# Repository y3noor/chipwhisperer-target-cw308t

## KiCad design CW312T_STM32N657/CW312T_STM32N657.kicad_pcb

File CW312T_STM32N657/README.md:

# CW312T STM32N657, rev 01

This four-layer CW312 card uses the STM32N657X0H3Q in the 264-ball VFBGA. It has SWD, USART1, and a 512-Mbit external serial NOR flash. Open the KiCad 10 project to edit the schematic and PCB. The BOM and all 64 CW312 contacts are in `bom.csv` and `cw312-pinout.csv`.

**Fabrication hold.** Complete the electrical and layout checks below before release.

## Power

Use a sequenced bench supply at J1.

| Pin | Supply |
| --- | --- |
| 1 | Ground |
| 2 | 3.3 V for VDD, VBAT, and the debug voltage reference |
| 3 | 1.8 V for VDDA18AON, PDR_ON, and VDDA18PLL |
| 4 | 1.8 V input for the switched auxiliary rail |

The 3.3 V and 1.8 V main domains must meet AN5967 rev 6 section 3.5. Use the supply's tracking or trigger function and verify the ramps at TP7 and TP8. During power-up, the AON threshold crossing can follow the VDD threshold crossing by up to 250 µs. While either rail exceeds 0.6 V, keep AON within 50 mV above VDD. Apply the main group before the auxiliary group.

J5 pins 1–2 connect the MCU's PWR_ON to the auxiliary switch. PWR_ON goes high after the main group reaches its thresholds. U2 then provides the 1.8 V auxiliary rail for VDDSMPS, VDDA18PMU through FB1, VDDIO3, and the flash. The internal SMPS produces the core rail through L1. The SMPS uses local input capacitors, the output capacitor bank, and the R4/C5 snubber from the AN5967 topology. V08CAP has a dedicated capacitor. USB and ADC supplies and unused VDDIO2, VDDIO4, and VDDIO5 are tied to ground. CSI supplies are grounded and CSI signals are open.

For controlled shutdown, set J5 to OFF by removing the 1–2 shunt or installing it on 2–3. R2 holds the switch off with the shunt removed. U2 discharges the auxiliary rail through QOD. The AON-powered U4 sinks current through R9 to discharge the core rail. Keep the main rails within range until TP9 and TP10 are below 0.6 V. Then lower VDD and AON under tracking control as specified in AN5967 section 3.5.2. Verify the full sequence for controlled shutdown and loss of input before release.

CW313 passes Husky's 200 mA target supply to A5. ST's AN6000 tests the core converter with load steps to 700 mA. At 0.81 V, that step is 0.57 W. At 85% efficiency it would draw about 203 mA from 3.3 V before adding any I/O, memory, or startup load. This is a sizing case. Measure the actual current at startup and under load. The card leaves CW313 supply and shunt inputs open. A26 is the target's debug voltage reference. Use a probe with a voltage-sense input. Power down or disconnect external signal drivers before switching off the target. Set CW313 I/O to high impedance until the target rail is up.

R1 is the removable 0 Ω link in the 1.8 V auxiliary input. With power off, remove R1 and connect an ammeter between TP1 and TP2. This measures U2 input current, including the internal core converter, VDDIO3, and external flash. It excludes the 3.3 V and 1.8 V main rails. Monitor TP9 as you measure. The switch and meter both cause voltage drop.

## Bring-up

1. Keep all power off. Align the key with the CW313 slot. The MCU side faces the CW313 component side. Seat the card with the same orientation as the RP2350 reference.
2. Set J5 to OFF. Apply the main rails and confirm TP7, TP8, and PWR_ON at TP11. Set J5 to RUN with the 1–2 shunt. Check TP9 for the auxiliary rail and TP10 for the core rail. Check NRST at TP4. TP3 is ground.
3. For development boot, fit a shunt across J4 pins 3–4 to raise BOOT1 and leave pins 1–2 open. Reset the target. Connect ST-LINK with SWD. J2 pins 1 through 5 are VTREF, GND, SWDIO, SWCLK, and NRST. TP5 and TP6 expose SWDIO and SWCLK. The same debug signals are on CW313's Cortex connector. Use one probe.
4. For serial boot, remove the BOOT1 shunt. Fit a shunt across J4 pins 1–2 to raise BOOT0. Reset the target. Use the 3.3 V USART1 interface on J3. J3.1 is ground, J3.2 is target TX, and J3.3 is target RX. Keep the Husky TX output at high impedance if an external adapter drives RX. ST lists PE5 and PE6 as ROM USART1 pins. The device life cycle and OTP settings determine which ROM boot paths are available.
5. For flash boot, remove both J4 shunts. The resistors select BOOT0=0 and BOOT1=0. Use a first-stage bootloader with the STM32 header and a board-specific external loader for the MX25UM51245G. The ROM reads serial NOR on XSPI1 through XSPIM port 2. Use the default single-SPI protocol for first bring-up. Verify the XSPI loader and timing before enabling octal or double data rate modes.
6. The board has a 48 MHz HSE crystal. Use the internal clocks for initial SWD checks and verify the crystal starts before relying on it. C7 and C8 are initial load values from the Nucleo circuit. Adjust after measuring crystal loading and startup margin. R10 is a DNP link for a clock source at TP12. Remove Y1 if you fit R10 and configure HSE bypass. Use LSI when the firmware needs a low-speed clock.
7. Configure PG8 as an output for the trigger on CW312 B19. Set CW313 JP2 to GPIO4 and configure the capture-side pin as an input.

## Mechanical and layout checks

The 64 contact pads match the template and RP2350 pad dimensions and center offsets to 0.0001 mm resolution. The 1.00 mm pitch increases to 3.00 mm across the key. The tongue span is 34.30 mm. The contact lands are 0.70 × 4.20 mm. The A row is on the back and the B row is on the component side. The card is 1.60 mm thick for the CW313 Samtec -02 slot. The board outline and contact positions follow the CW312 template. The nearest fitted component is more than 4 mm from the end of a contact land. Confirm seating, insertion force, and probe access with a first article.

The BGA has a 14 × 14 mm body, a 0.80 mm grid, 0.40 mm lands, and 0.47 mm mask openings. The board uses four copper layers at 1.60 mm thickness. Layers 1 and 4 carry components, traces, and ground pours. Layer 2 carries the main ground pour and some traces. Layer 3 carries separate core and auxiliary supply pours and some traces. BGA escape uses plated through vias with a 0.20 mm minimum drill and a 0.125 mm minimum trace width. Check return paths around the traces and plane openings before fabrication.

KiCad 10.0.6 ERC and DRC report zero violations. DRC also reports zero unrouted pads and zero schematic parity issues.

The serial NOR has the same memory family and port assignment as the Nucleo design. This board uses the orderable SOIC-16W variant, with a 133 MHz part rating. The routed CLK, DQS, and IO0–IO7 copper lengths range from 6.10 to 25.25 mm, before via and package lengths. The Nucleo reference targets 1.27 mm matching for high-speed operation. The current routing requires length and return-path review before release. Confirm the PCB stackup and evaluate the flash timing at the intended clock rate with the selected assembly process. Review the core and auxiliary copper for IR drop at startup and full load. Verify the SMPS feedback route and snubber layout. Validate BGA solder mask and drill tolerances with the fabricator. No fabrication files are issued during the hold.

For the first article, verify the sequenced rise and discharge of all rails, HSE startup, SWD attachment, USART1 serial boot, flash identification and erase/write/read, flash boot, and current at idle and under load. Also verify the behavior when external signal cables are connected and the target powers down.

## References

- NewAE CW312 template rev 0, commit `40c337d2c8c15345bab03c9aa2072a23a36ccc3b`. The template license field says TBD. The CW312T_RP2350 rev 02 project is marked NDA. Contact and outline dimensions were measured and redrawn in KiCad.
- NewAE CW313 rev 02 schematic and PCB, commit `7b689277ca6852fccd195c29525a26640b6296d0`. The schematic title block states CC SA 3.0. [CW313 design files](https://github.com/newaetech/chipwhisperer-target-cw313/tree/7b689277ca6852fccd195c29525a26640b6296d0)
- Samtec PCIE-XXX-02-X-D-RA series drawing, sheets 1 and 2. [Connector drawing](https://suddendocs.samtec.com/prints/pcie-xxx-02-x-d-ra-mkt.pdf)
- ST MB1940-N657X0Q-C02, rev C-02. Sheets 3–5, 9, 12, and 14 cover I/O, power, flash, reset, and debug. The cover refers to ST's Open Platform License Agreement. The design uses reference circuit information and original KiCad artwork. [Nucleo schematic](https://www.st.com/resource/en/schematic_pack/mb1940-n657x0q-c02-schematic.pdf)
- ST DS14791 rev 11, plus the rev 2 package drawing and table 123 for the VFBGA264 land pattern. [STM32N657 datasheet](https://www.st.com/resource/en/datasheet/stm32n657x0.pdf)
- ST STM32 Open Pin Data, `mcu/STM32N657X0HxQ.xml`, commit `45c04599e2e0a788c5ed9b6218dc5a28a36041f7`. The symbol and footprint use the package's ball names and positions. See the included BSD 3-Clause license. [Pin data](https://github.com/STMicroelectronics/STM32_open_pin_data/blob/45c04599e2e0a788c5ed9b6218dc5a28a36041f7/mcu/STM32N657X0HxQ.xml)
- ST AN5967 rev 6, sections 3.4 through 3.6, for the power groups and timing. [Hardware development guide](https://www.st.com/resource/en/application_note/an5967-getting-started-with-hardware-development-for-stm32n6-mcus-stmicroelectronics.pdf)
- ST UM3234, serial NOR boot and USART1 pin assignment. [Boot ROM guide](https://www.st.com/resource/en/user_manual/um3234-how-to-proceed-with-boot-rom-on-stm32n6-mcus-stmicroelectronics.pdf)
- ST AN6000, core load transient specification. [Power supply guide](https://www.st.com/content/st_com/en/technical-documents/an6000-how-to-build-the-discrete-power-supply-for-stm32n6-mcus-stmicroelectronics.html)
- Macronix PM2183 rev 1.6, pin assignments, power, and ordering information. [Flash datasheet](https://www.macronix.com/Lists/Datasheet/Attachments/9241/MX25UM51245G%2C%201.8V%2C%20512Mb%2C%20v1.6.pdf)
- Texas Instruments SLVSD76C, TPS22918 load switch with QOD. [Load switch datasheet](https://www.ti.com/lit/ds/symlink/tps22918.pdf)

The ST-hosted PDF downloads for the Nucleo schematic and current datasheet, hardware guide, and boot ROM guide failed in this environment. Their contents were reviewed online. The local reference directory includes the available older ST revisions and the other downloaded reference PDFs.

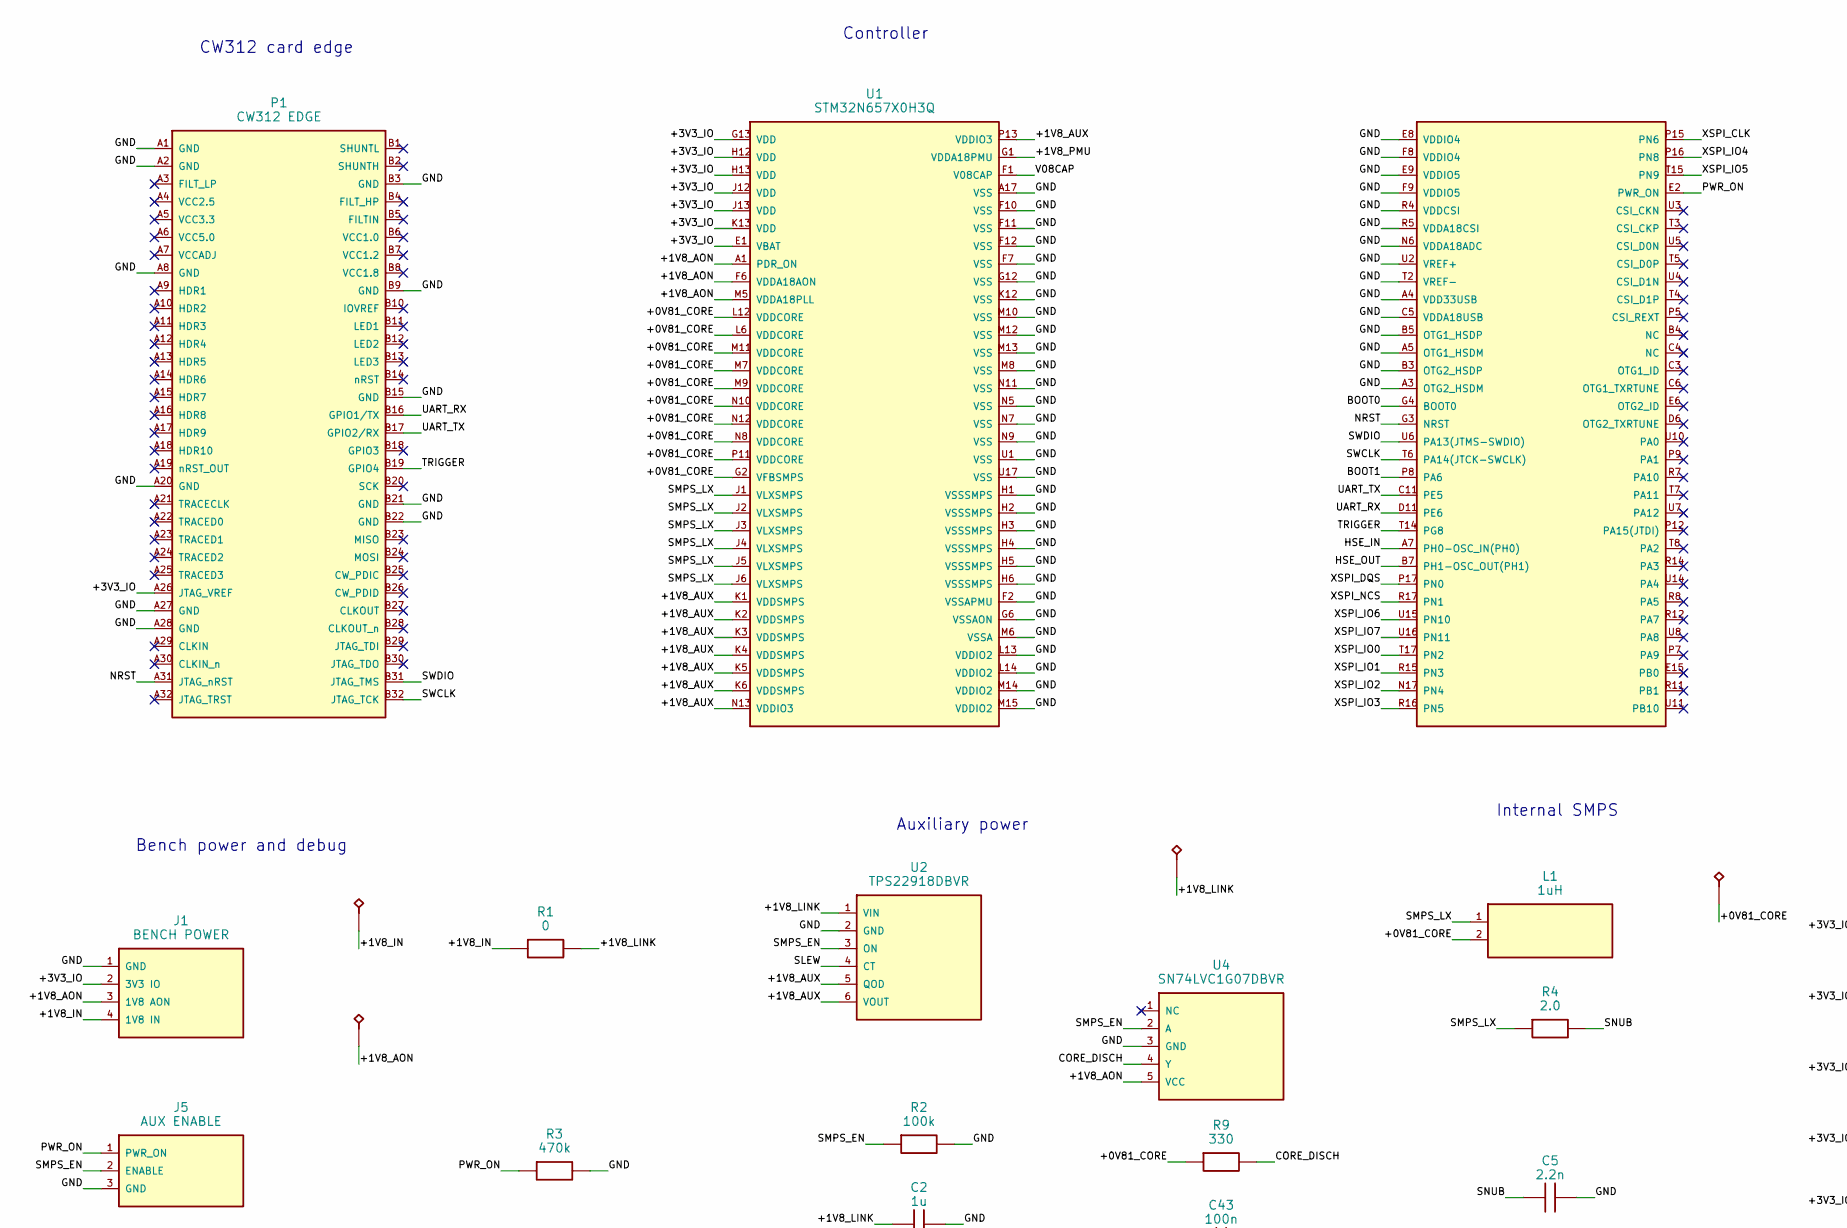
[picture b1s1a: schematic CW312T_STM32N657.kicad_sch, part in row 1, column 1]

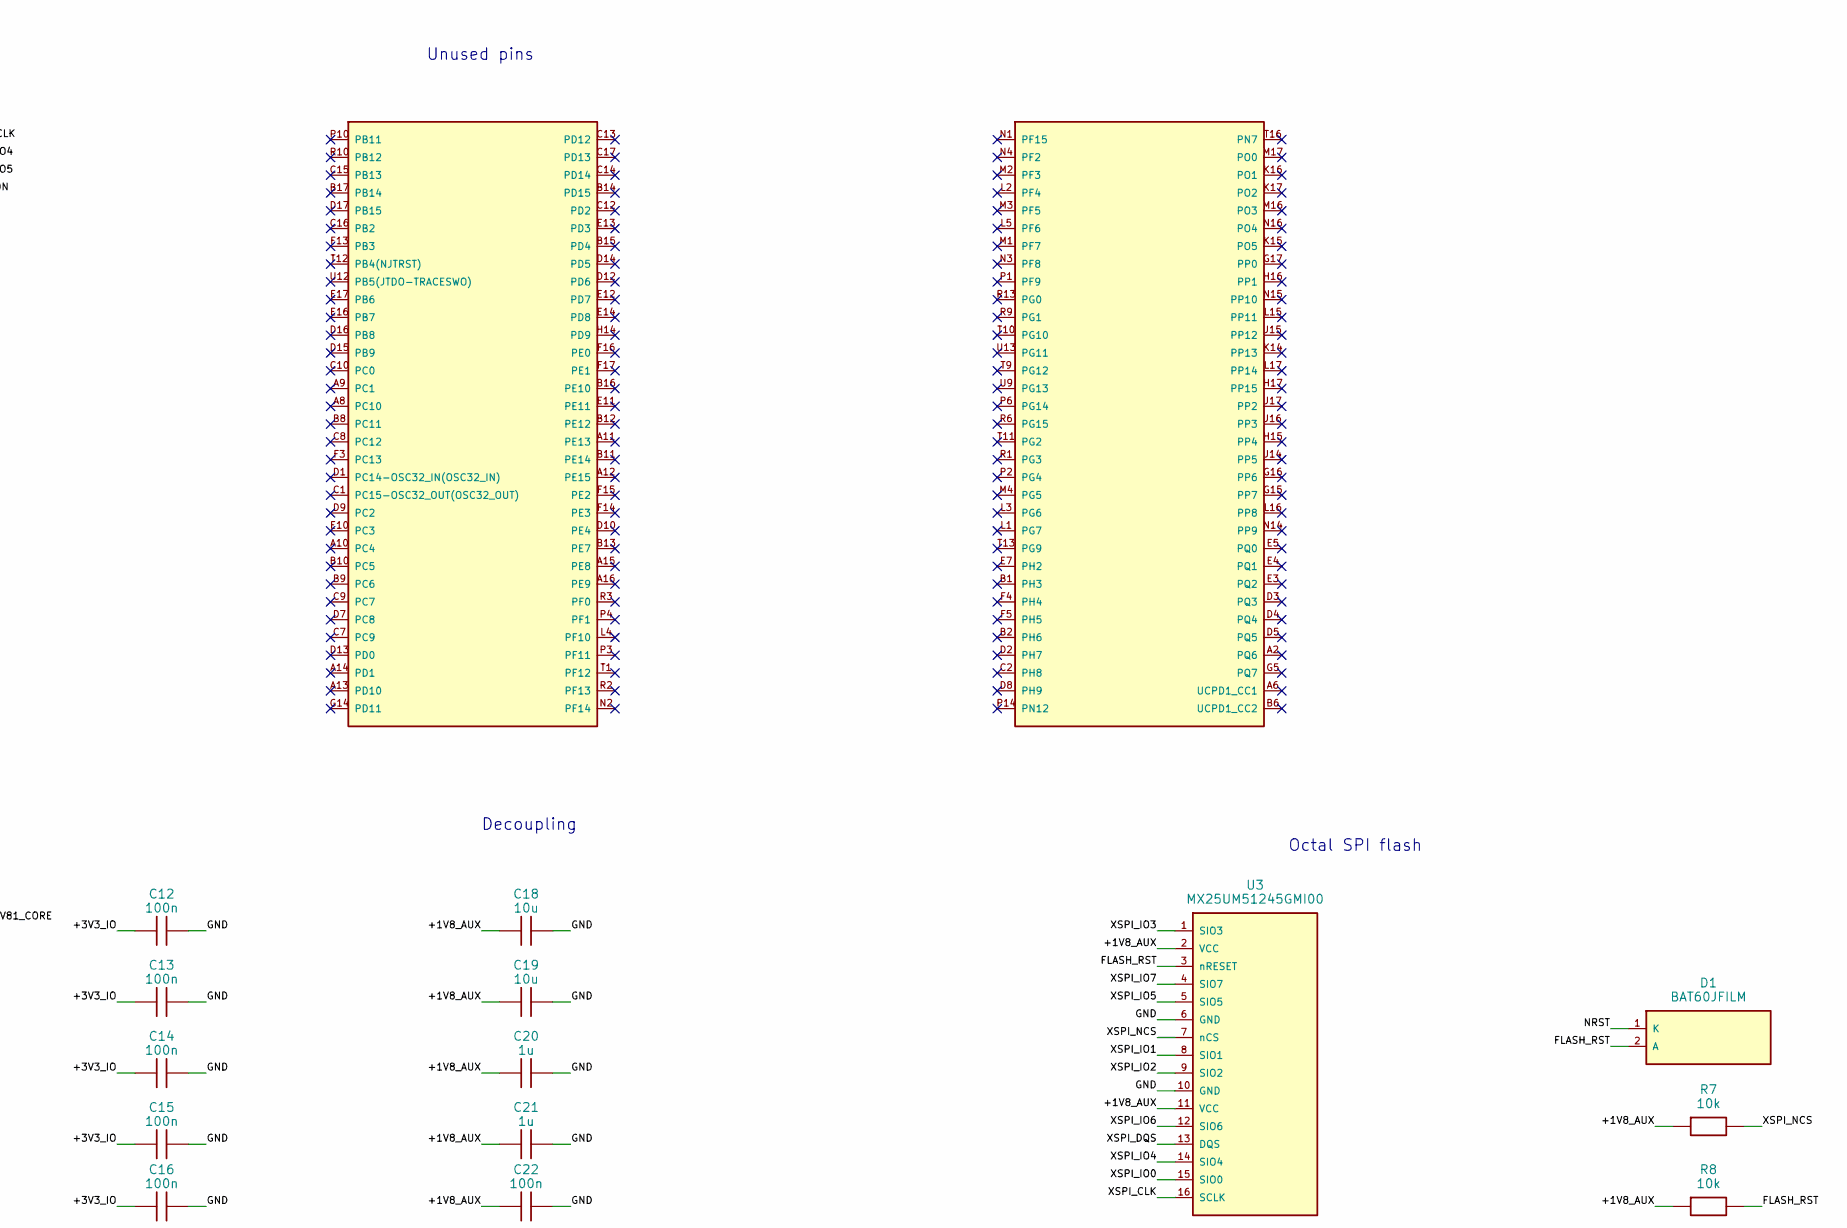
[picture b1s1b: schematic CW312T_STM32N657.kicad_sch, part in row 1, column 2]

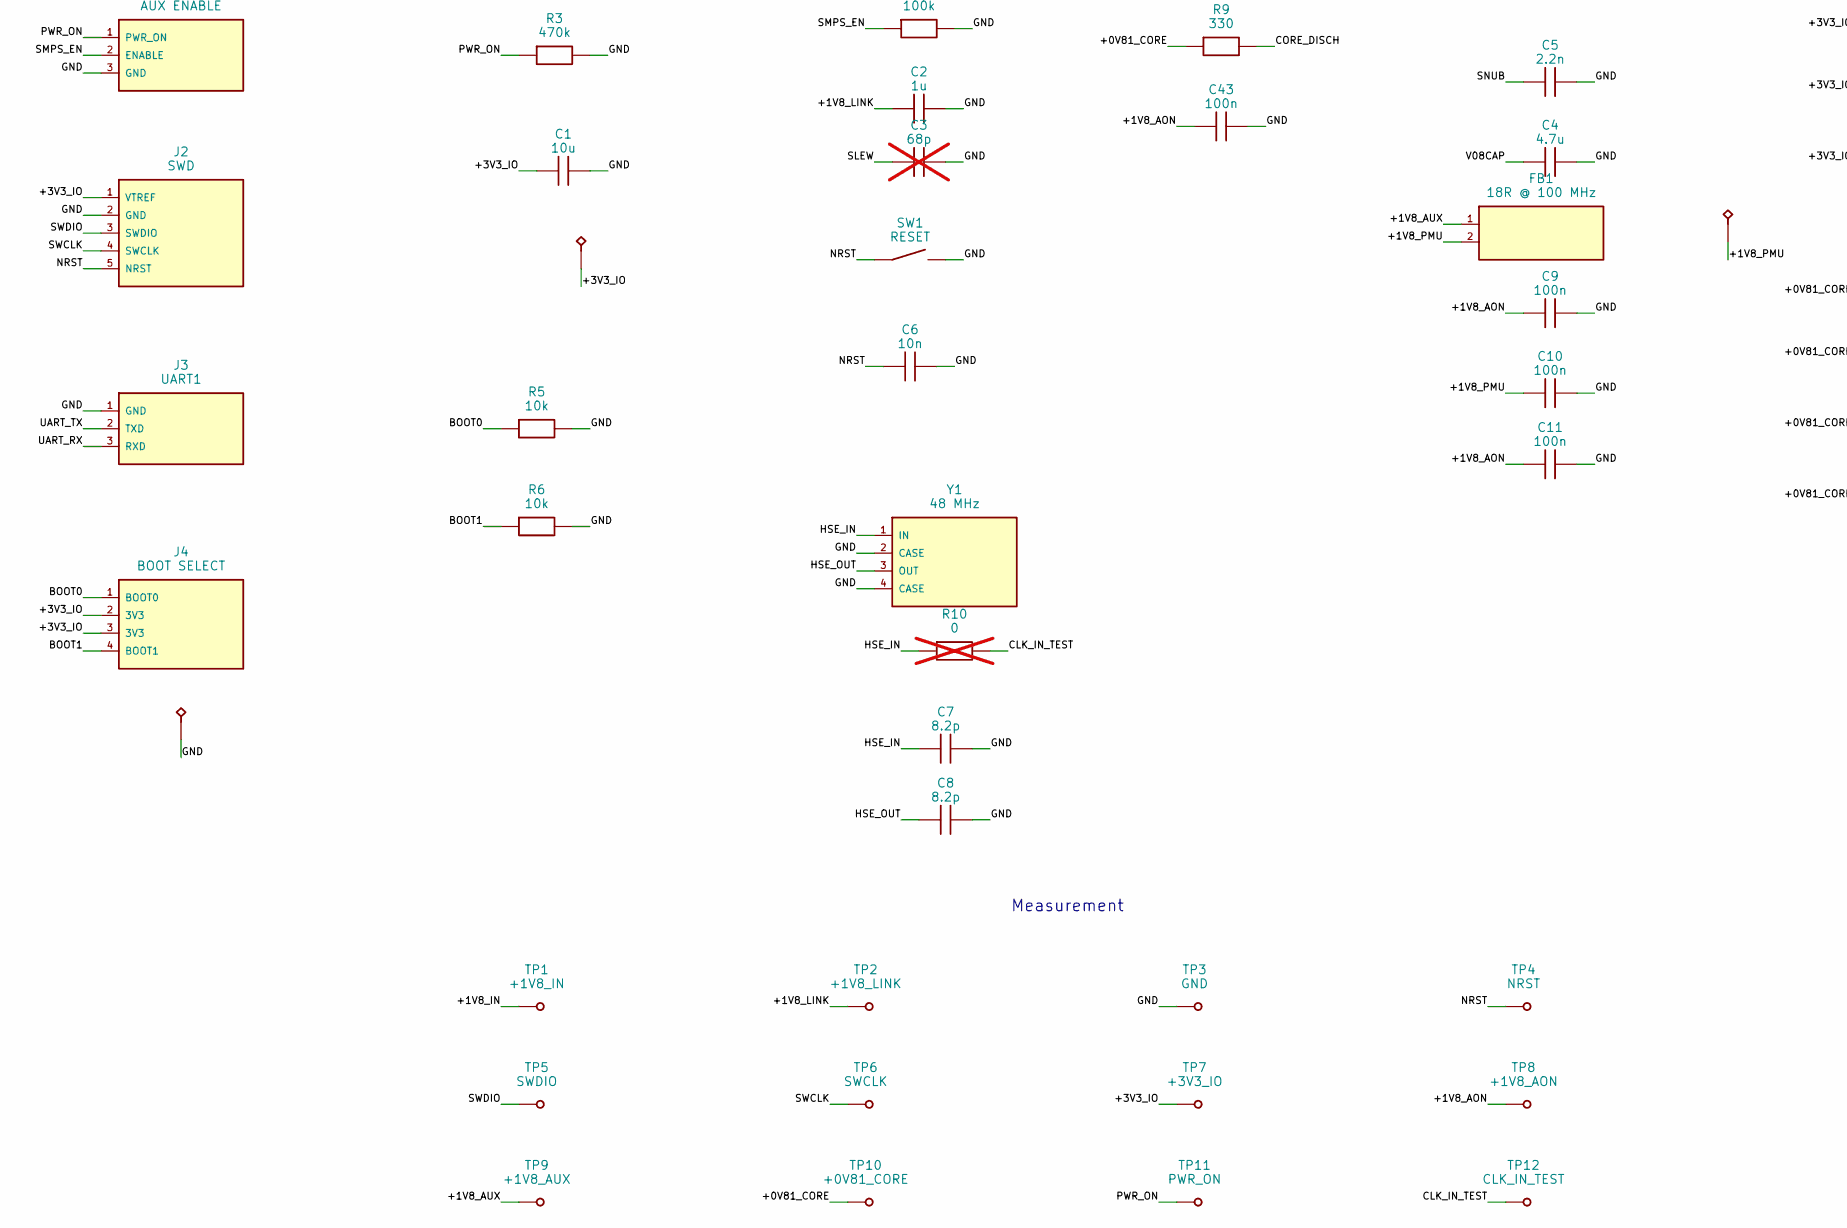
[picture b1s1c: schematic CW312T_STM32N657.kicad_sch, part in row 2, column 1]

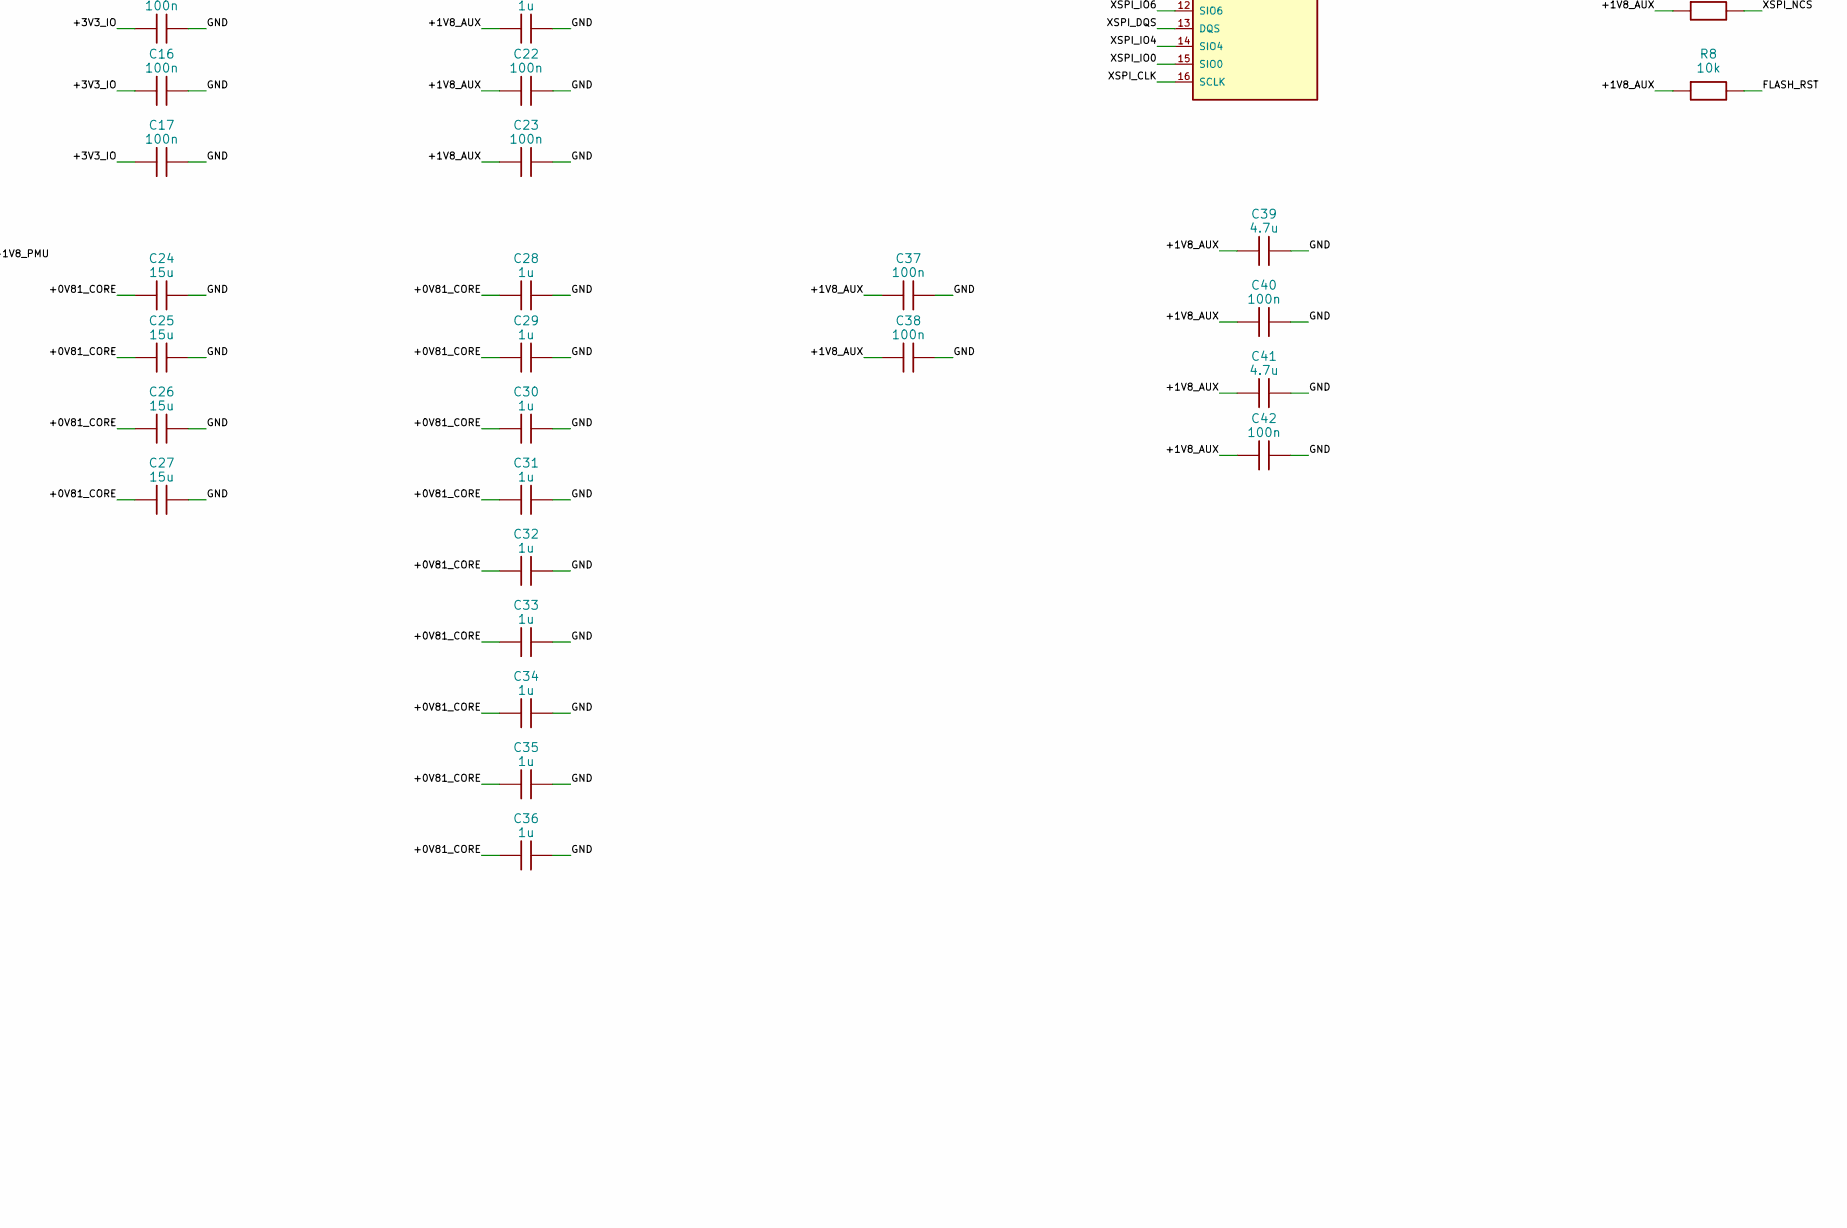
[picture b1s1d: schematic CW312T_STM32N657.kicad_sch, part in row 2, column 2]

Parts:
C1, C18, C19: 10u; C_0805_2012Metric
C2, C20, C21, C28, C29, C30, C31, C32, C33, C34, C35, C36: 1u; C_0402_1005Metric
C3: 68p; C_0402_1005Metric; not fitted
C4, C39, C41: 4.7u; C_0603_1608Metric
C5: 2.2n; C_0603_1608Metric
C6: 10n; C_0402_1005Metric
C7, C8: 8.2p; C_0402_1005Metric
C9, C10, C11, C12, C13, C14, C15, C16, C17, C22, C23, C37, C38, C40, C42, C43: 100n; C_0402_1005Metric
C24, C25, C26, C27: 15u; C_0805_2012Metric
D1: BAT60JFILM; D_SOD-323
FB1: 18R @ 100 MHz; L_0603_1608Metric
J1: BENCH POWER; PinHeader_1x04_P2.54mm_Vertical
J2: SWD; PinHeader_1x05_P2.54mm_Vertical
J3: UART1; PinHeader_1x03_P2.54mm_Vertical
J4: BOOT SELECT; PinHeader_1x04_P2.54mm_Vertical
J5: AUX ENABLE; PinHeader_1x03_P2.54mm_Vertical
L1: 1uH; L_1210_3225Metric
P1: CW312 EDGE; CW312
R1: 0; R_1206_3216Metric
R2: 100k; R_0603_1608Metric
R3: 470k; R_0603_1608Metric
R4: 2.0; R_0603_1608Metric
R5, R6, R7, R8: 10k; R_0603_1608Metric
R9: 330; R_0603_1608Metric
R10: 0; R_0603_1608Metric; not fitted
SW1: RESET; SW_Tactile_SPST_NO_Straight_CK_PTS636Sx25SMTRLFS
TP1: +1V8_IN; TestPoint_Pad_D1.5mm
TP2: +1V8_LINK; TestPoint_Pad_D1.5mm
TP3: GND; TestPoint_Pad_D1.5mm
TP4: NRST; TestPoint_Pad_D1.5mm
TP5: SWDIO; TestPoint_Pad_D1.5mm
TP6: SWCLK; TestPoint_Pad_D1.5mm
TP7: +3V3_IO; TestPoint_Pad_D1.5mm
TP8: +1V8_AON; TestPoint_Pad_D1.5mm
TP9: +1V8_AUX; TestPoint_Pad_D1.5mm
TP10: +0V81_CORE; TestPoint_Pad_D1.5mm
TP11: PWR_ON; TestPoint_Pad_D1.5mm
TP12: CLK_IN_TEST; TestPoint_Pad_D1.5mm
U1: STM32N657X0H3Q; ST_VFBGA-264_14x14mm_Layout17x17_P0.8mm
U2: TPS22918DBVR; SOT-23-6
U3: MX25UM51245GMI00; SOIC-16W_7.5x10.3mm_P1.27mm
U4: SN74LVC1G07DBVR; SOT-23-5
Y1: 48 MHz; Crystal_SMD_2016-4Pin_2.0x1.6mm

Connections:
/+0V81_CORE: C24.1, C25.1, C26.1, C27.1, C28.1, C29.1, C30.1, C31.1, C32.1, C33.1, C34.1, C35.1, C36.1, L1.2, R9.1, TP10.1, U1.G2 (VFBSMPS), U1.L6 (VDDCORE), U1.L12 (VDDCORE), U1.M7 (VDDCORE), U1.M9 (VDDCORE), U1.M11 (VDDCORE), U1.N8 (VDDCORE), U1.N10 (VDDCORE), U1.N12 (VDDCORE), U1.P11 (VDDCORE)
/+1V8_AON: C9.1, C11.1, C43.1, J1.3 (1V8_AON), TP8.1, U1.A1 (PDR_ON), U1.F6 (VDDA18AON), U1.M5 (VDDA18PLL), U4.5 (VCC)
/+1V8_AUX: C18.1, C19.1, C20.1, C21.1, C22.1, C23.1, C37.1, C38.1, C39.1, C40.1, C41.1, C42.1, FB1.1, R7.1, R8.1, TP9.1, U1.K1 (VDDSMPS), U1.K2 (VDDSMPS), U1.K3 (VDDSMPS), U1.K4 (VDDSMPS), U1.K5 (VDDSMPS), U1.K6 (VDDSMPS), U1.N13 (VDDIO3), U1.P13 (VDDIO3), U2.5 (QOD), U2.6 (VOUT), U3.2 (VCC), U3.11 (VCC)
/+1V8_IN: J1.4 (1V8_IN), R1.1, TP1.1
/+1V8_LINK: C2.1, R1.2, TP2.1, U2.1 (VIN)
/+1V8_PMU: C10.1, FB1.2, U1.G1 (VDDA18PMU)
/+3V3_IO: C1.1, C12.1, C13.1, C14.1, C15.1, C16.1, C17.1, J1.2 (3V3_IO), J2.1 (VTREF), J4.2 (3V3), J4.3 (3V3), P1.A26 (JTAG_VREF), TP7.1, U1.E1 (VBAT), U1.G13 (VDD), U1.H12 (VDD), U1.H13 (VDD), U1.J12 (VDD), U1.J13 (VDD), U1.K13 (VDD)
/BOOT0: J4.1 (BOOT0), R5.1, U1.G4 (BOOT0)
/BOOT1: J4.4 (BOOT1), R6.1, U1.P8 (PA6)
/CLK_IN_TEST: R10.2, TP12.1
/CORE_DISCH: R9.2, U4.4 (Y)
/FLASH_RST: D1.2 (A), R8.2, U3.3 (nRESET)
/GND: C1.2, C2.2, C3.2, C4.2, C5.2, C6.2, C7.2, C8.2, C9.2, C10.2, C11.2, C12.2, C13.2, C14.2, C15.2, C16.2, C17.2, C18.2, C19.2, C20.2, C21.2, C22.2, C23.2, C24.2, C25.2, C26.2, C27.2, C28.2, C29.2, C30.2, C31.2, C32.2, C33.2, C34.2, C35.2, C36.2, C37.2, C38.2, C39.2, C40.2, C41.2, C42.2, C43.2, J1.1 (GND), J2.2 (GND), J3.1 (GND), J5.3 (GND), P1.A1 (GND), P1.A2 (GND), P1.A8 (GND), P1.A20 (GND), P1.A27 (GND), P1.A28 (GND), P1.B3 (GND), P1.B9 (GND), P1.B15 (GND), P1.B21 (GND), P1.B22 (GND), R2.2, R3.2, R5.2, R6.2, SW1.2, TP3.1, U1.A3 (OTG2_HSDM), U1.A4 (VDD33USB), U1.A5 (OTG1_HSDM), U1.A17 (VSS), U1.B3 (OTG2_HSDP), U1.B5 (OTG1_HSDP), U1.C5 (VDDA18USB), U1.E8 (VDDIO4), U1.E9 (VDDIO5), U1.F2 (VSSAPMU), U1.F7 (VSS), U1.F8 (VDDIO4), U1.F9 (VDDIO5), U1.F10 (VSS), U1.F11 (VSS), U1.F12 (VSS), U1.G6 (VSSAON), U1.G12 (VSS), U1.H1 (VSSSMPS), U1.H2 (VSSSMPS), U1.H3 (VSSSMPS), U1.H4 (VSSSMPS), U1.H5 (VSSSMPS), U1.H6 (VSSSMPS), U1.K12 (VSS), U1.L13 (VDDIO2), U1.L14 (VDDIO2), U1.M6 (VSSA), U1.M8 (VSS), U1.M10 (VSS), U1.M12 (VSS), U1.M13 (VSS), U1.M14 (VDDIO2), U1.M15 (VDDIO2), U1.N5 (VSS), U1.N6 (VDDA18ADC), U1.N7 (VSS), U1.N9 (VSS), U1.N11 (VSS), U1.R4 (VDDCSI), U1.R5 (VDDA18CSI), U1.T2 (VREF-), U1.U1 (VSS), U1.U2 (VREF+), U1.U17 (VSS), U2.2 (GND), U3.6 (GND), U3.10 (GND), U4.3 (GND), Y1.2 (CASE), Y1.4 (CASE)
/HSE_IN: C7.1, R10.1, U1.A7 (PH0-OSC_IN(PH0)), Y1.1 (IN)
/HSE_OUT: C8.1, U1.B7 (PH1-OSC_OUT(PH1)), Y1.3 (OUT)
/NRST: C6.1, D1.1 (K), J2.5 (NRST), P1.A31 (JTAG_nRST), SW1.1, TP4.1, U1.G3 (NRST)
/PWR_ON: J5.1 (PWR_ON), R3.1, TP11.1, U1.E2 (PWR_ON)
/SLEW: C3.1, U2.4 (CT)
/SMPS_EN: J5.2 (ENABLE), R2.1, U2.3 (ON), U4.2 (A)
/SMPS_LX: L1.1, R4.1, U1.J1 (VLXSMPS), U1.J2 (VLXSMPS), U1.J3 (VLXSMPS), U1.J4 (VLXSMPS), U1.J5 (VLXSMPS), U1.J6 (VLXSMPS)
/SNUB: C5.1, R4.2
/SWCLK: J2.4 (SWCLK), P1.B32 (JTAG_TCK), TP6.1, U1.T6 (PA14(JTCK-SWCLK))
/SWDIO: J2.3 (SWDIO), P1.B31 (JTAG_TMS), TP5.1, U1.U6 (PA13(JTMS-SWDIO))
/TRIGGER: P1.B19 (GPIO4), U1.T14 (PG8)
/UART_RX: J3.3 (RXD), P1.B16 (GPIO1/TX), U1.D11 (PE6)
/UART_TX: J3.2 (TXD), P1.B17 (GPIO2/RX), U1.C11 (PE5)
/V08CAP: C4.1, U1.F1 (V08CAP)
/XSPI_CLK: U1.P15 (PN6), U3.16 (SCLK)
/XSPI_DQS: U1.P17 (PN0), U3.13 (DQS)
/XSPI_IO0: U1.T17 (PN2), U3.15 (SIO0)
/XSPI_IO1: U1.R15 (PN3), U3.8 (SIO1)
/XSPI_IO2: U1.N17 (PN4), U3.9 (SIO2)
/XSPI_IO3: U1.R16 (PN5), U3.1 (SIO3)
/XSPI_IO4: U1.P16 (PN8), U3.14 (SIO4)
/XSPI_IO5: U1.T15 (PN9), U3.5 (SIO5)
/XSPI_IO6: U1.U15 (PN10), U3.12 (SIO6)
/XSPI_IO7: U1.U16 (PN11), U3.4 (SIO7)
/XSPI_NCS: R7.2, U1.R17 (PN1), U3.7 (nCS)

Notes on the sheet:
CW312 card edge
Controller
Unused pins
Bench power and debug
Auxiliary power
Internal SMPS
Decoupling
Octal SPI flash
Measurement

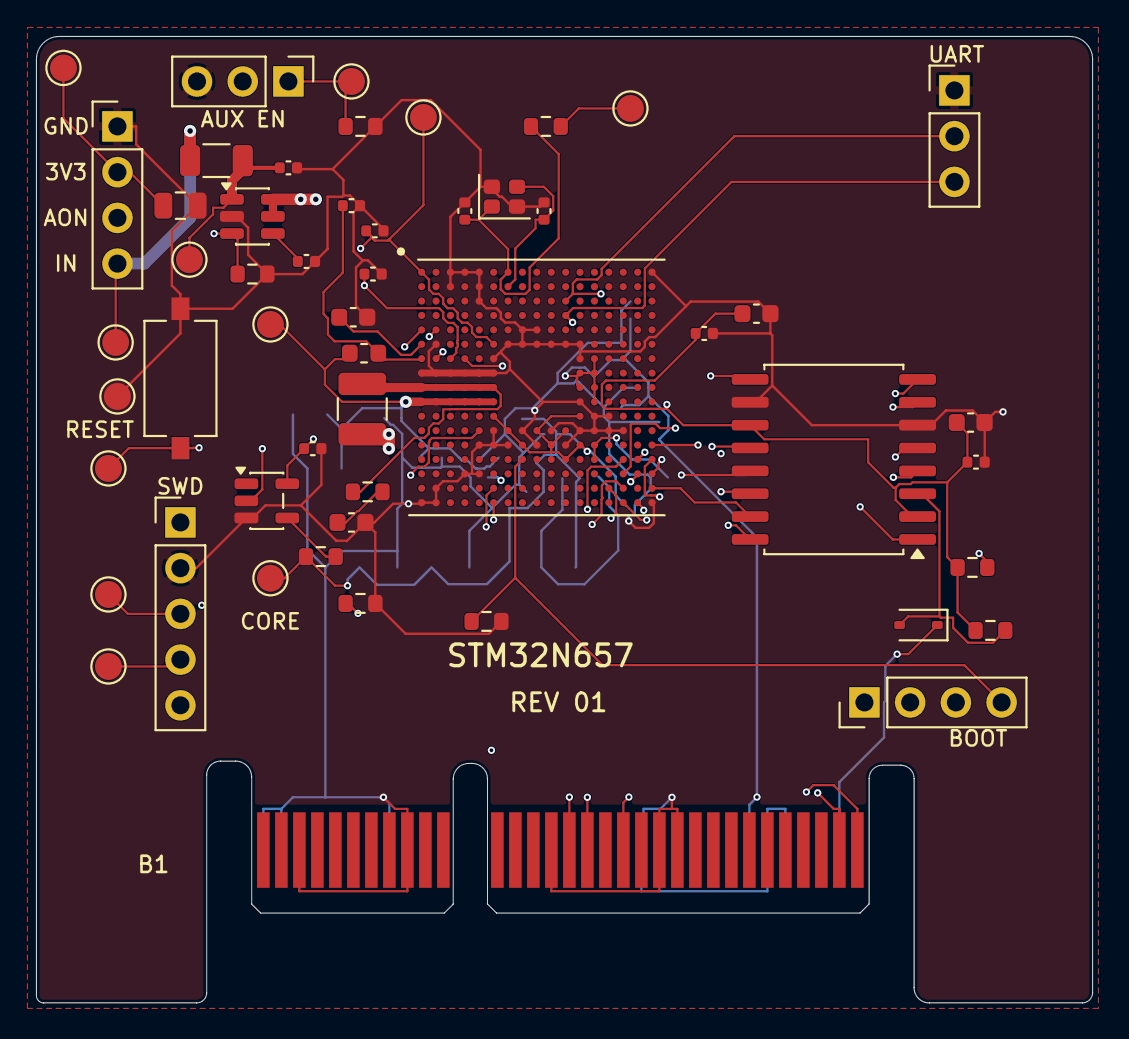
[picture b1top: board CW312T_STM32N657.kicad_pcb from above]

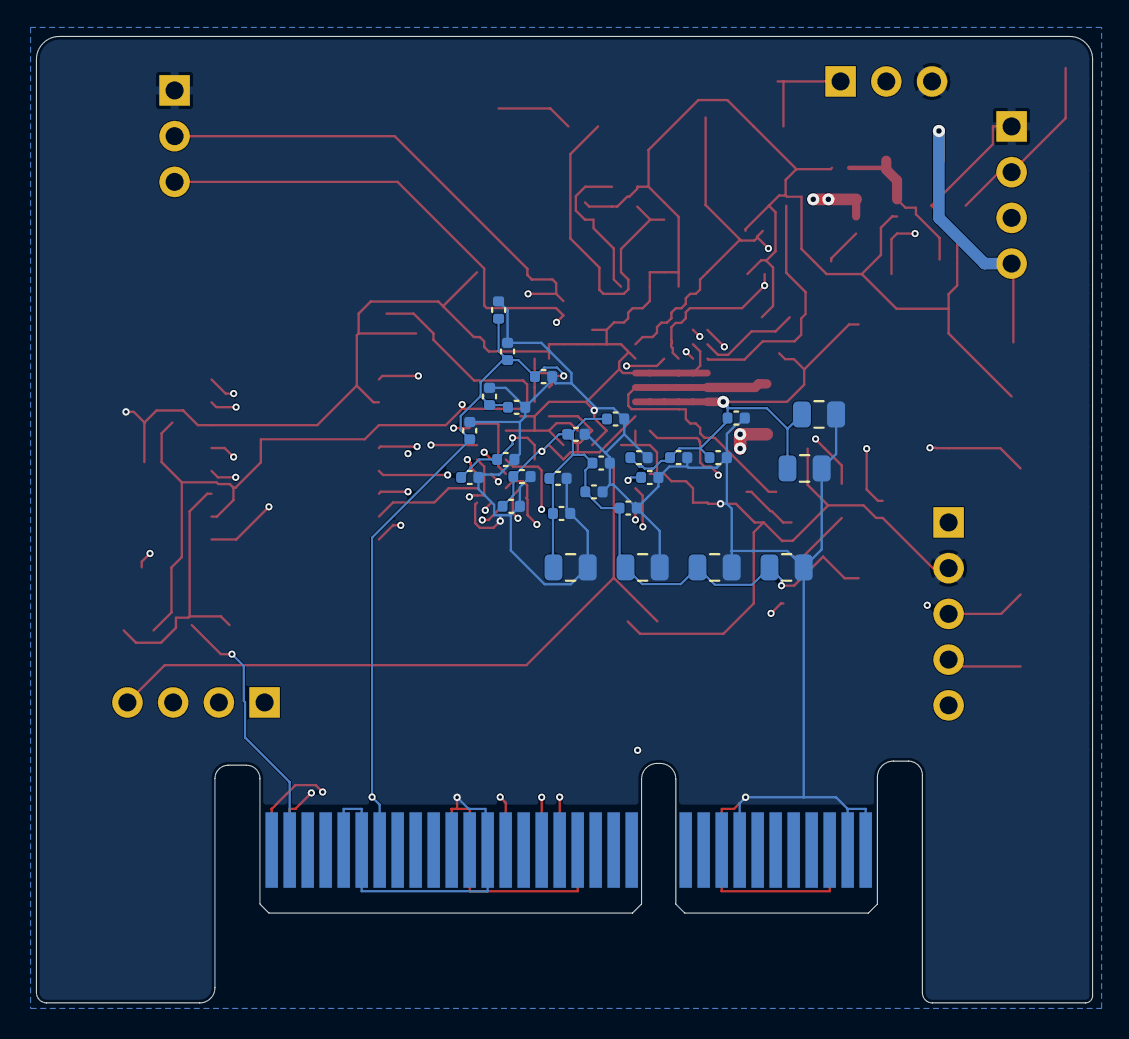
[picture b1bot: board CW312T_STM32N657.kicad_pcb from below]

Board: 4 copper layers, 58.7 x 53.7 mm, 80 parts (28 on the bottom side), 38 nets.

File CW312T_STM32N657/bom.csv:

Reference,Value,Manufacturer,Manufacturer part number,Package,Qty fitted,DNP
C1,10u,Murata,GRM21BR71A106KE51L,0805,1,No
C2,1u,Murata,GRM155R60J105KE19D,0402,1,No
C3,68p,Murata,GRM1555C1H680JA01D,0402,0,Yes
C4,4.7u,Murata,GRM188R60J475KE19D,0603,1,No
C5,2.2n,Murata,GRM188R71H222KA01D,0603,1,No
C6,10n,Murata,GRM155R71H103KA88D,0402,1,No
C7,8.2p,Murata,GRM1555C1H8R2CA01D,0402,1,No
C8,8.2p,Murata,GRM1555C1H8R2CA01D,0402,1,No
C9,100n,Murata,GRM155R71A104KA01D,0402,1,No
C10,100n,Murata,GRM155R71A104KA01D,0402,1,No
C11,100n,Murata,GRM155R71A104KA01D,0402,1,No
C12,100n,Murata,GRM155R71A104KA01D,0402,1,No
C13,100n,Murata,GRM155R71A104KA01D,0402,1,No
C14,100n,Murata,GRM155R71A104KA01D,0402,1,No
C15,100n,Murata,GRM155R71A104KA01D,0402,1,No
C16,100n,Murata,GRM155R71A104KA01D,0402,1,No
C17,100n,Murata,GRM155R71A104KA01D,0402,1,No
C18,10u,Murata,GRM21BR71A106KE51L,0805,1,No
C19,10u,Murata,GRM21BR71A106KE51L,0805,1,No
C20,1u,Murata,GRM155R60J105KE19D,0402,1,No
C21,1u,Murata,GRM155R60J105KE19D,0402,1,No
C22,100n,Murata,GRM155R71A104KA01D,0402,1,No
C23,100n,Murata,GRM155R71A104KA01D,0402,1,No
C24,15u,Murata,GRM21BR60J156ME19L,0805,1,No
C25,15u,Murata,GRM21BR60J156ME19L,0805,1,No
C26,15u,Murata,GRM21BR60J156ME19L,0805,1,No
C27,15u,Murata,GRM21BR60J156ME19L,0805,1,No
C28,1u,Murata,GRM155R60J105KE19D,0402,1,No
C29,1u,Murata,GRM155R60J105KE19D,0402,1,No
C30,1u,Murata,GRM155R60J105KE19D,0402,1,No
C31,1u,Murata,GRM155R60J105KE19D,0402,1,No
C32,1u,Murata,GRM155R60J105KE19D,0402,1,No
C33,1u,Murata,GRM155R60J105KE19D,0402,1,No
C34,1u,Murata,GRM155R60J105KE19D,0402,1,No
C35,1u,Murata,GRM155R60J105KE19D,0402,1,No
C36,1u,Murata,GRM155R60J105KE19D,0402,1,No
C37,100n,Murata,GRM155R71A104KA01D,0402,1,No
C38,100n,Murata,GRM155R71A104KA01D,0402,1,No
C39,4.7u,Murata,GRM188R60J475KE19D,0603,1,No
C40,100n,Murata,GRM155R71A104KA01D,0402,1,No
C41,4.7u,Murata,GRM188R60J475KE19D,0603,1,No
C42,100n,Murata,GRM155R71A104KA01D,0402,1,No
C43,100n,Murata,GRM155R71A104KA01D,0402,1,No
D1,BAT60JFILM,STMicroelectronics,BAT60JFILM,SOD-323,1,No
FB1,18R @ 100 MHz,Murata,BLM18PG181SN1D,0603,1,No
J1,BENCH POWER,Samtec,TSW-104-07-G-S,2.54 mm THT 1x4,1,No
J2,SWD,Samtec,TSW-105-07-G-S,2.54 mm THT 1x5,1,No
J3,UART1,Samtec,TSW-103-07-G-S,2.54 mm THT 1x3,1,No
J4,BOOT SELECT,Samtec,TSW-104-07-G-S,2.54 mm THT 1x4,1,No
J5,AUX ENABLE,Samtec,TSW-103-07-G-S,2.54 mm THT 1x3,1,No
L1,1uH,TDK,TFM322512ALVA1R0MTAA,1210,1,No
R1,0,Yageo,RC1206JR-070RL,1206,1,No
R2,100k,Yageo,RC0603FR-07100KL,0603,1,No
R3,470k,Yageo,RC0603FR-07470KL,0603,1,No
R4,2.0,Yageo,RC0603FR-072RL,0603,1,No
R5,10k,Yageo,RC0603FR-0710KL,0603,1,No
R6,10k,Yageo,RC0603FR-0710KL,0603,1,No
R7,10k,Yageo,RC0603FR-0710KL,0603,1,No
R8,10k,Yageo,RC0603FR-0710KL,0603,1,No
R9,330,Yageo,RC0603FR-07330RL,0603,1,No
R10,0,Yageo,RC0603JR-070RL,0603,0,Yes
SW1,RESET,C&K,PTS636SK25SMTR LFS,6 x 3.5 mm SMD,1,No
U1,STM32N657X0H3Q,STMicroelectronics,STM32N657X0H3Q,"VFBGA264 14 x 14 mm, 0.8 mm pitch",1,No
U2,TPS22918DBVR,Texas Instruments,TPS22918DBVR,SOT-23-6,1,No
U3,MX25UM51245GMI00,Macronix,MX25UM51245GMI00,"SOIC-16W, 300 mil",1,No
U4,SN74LVC1G07DBVR,Texas Instruments,SN74LVC1G07DBVR,SOT-23-5,1,No
Y1,48 MHz,Abracon,ABM11W-48.0000MHZ-8-B1U-T3,"2016, 4 pad",1,No
HW1,J5 RUN shunt,Samtec,SNT-100-BK-G,2.54 mm shunt,1,No
HW2,J4 BOOT0 shunt,Samtec,SNT-100-BK-G,2.54 mm shunt,0,Yes
HW3,J4 BOOT1 shunt,Samtec,SNT-100-BK-G,2.54 mm shunt,0,Yes
